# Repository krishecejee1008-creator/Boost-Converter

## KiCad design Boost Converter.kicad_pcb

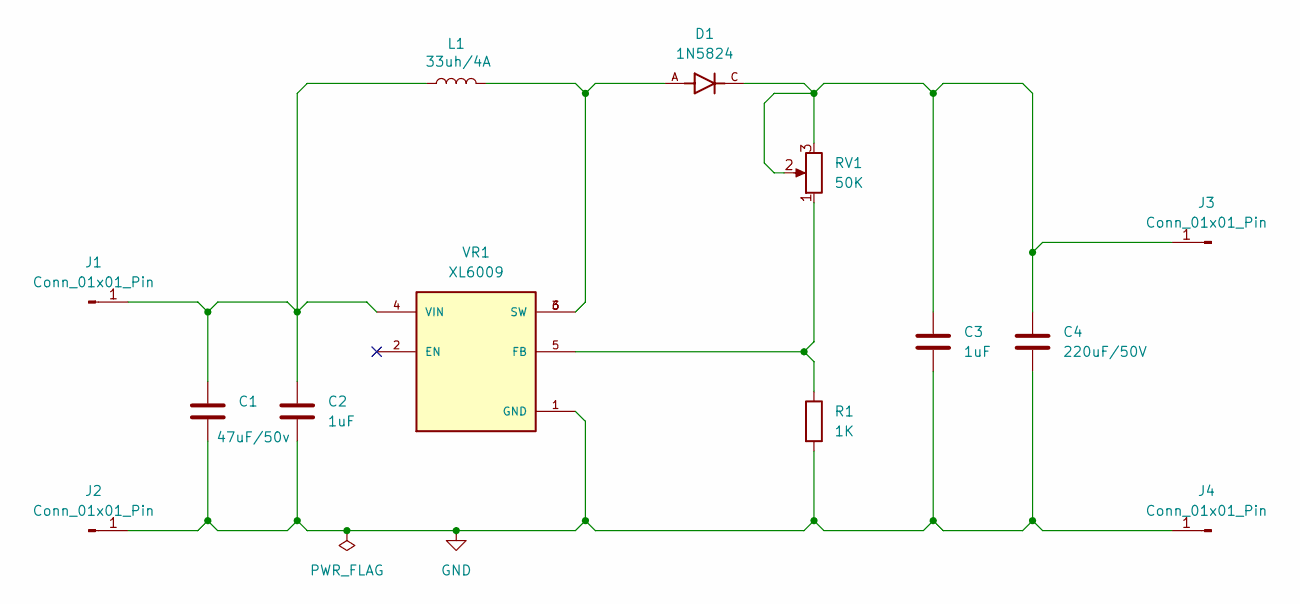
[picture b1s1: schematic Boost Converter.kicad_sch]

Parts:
C1: 47uF/50v; C_Radial_D6.3mm_H11.0mm_P2.50mm
C2, C3: 1uF; C_0805_2012Metric
C4: 220uF/50V; C_Radial_D6.3mm_H11.0mm_P2.50mm
D1: 1N5824; DIOAD1898W129L762D1143; PARTREV 2
J1, J2, J3, J4: Conn_01x01_Pin; PinHeader_1x01_P1.00mm_Vertical
L1: 33uh/4A; L_12x12mm_H8mm
R1: 1K; R_1206_3216Metric
RV1: 50K; Potentiometer_Bourns_3296W_Vertical
VR1: XL6009; DPAK170P1435X465-6N; PARTREV 1.1

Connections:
GND: C1.2, C2.2, C3.2, C4.2, J2.1, J4.1, R1.2, VR1.1 (GND)
unnamed: D1.A, L1.2, VR1.3 (SW), VR1.6 (SW)
unnamed: C1.1, C2.1, J1.1, L1.1, VR1.4 (VIN)
unnamed: C3.1, C4.1, D1.C, J3.1, RV1.2, RV1.3
unnamed: R1.1, RV1.1, VR1.5 (FB)

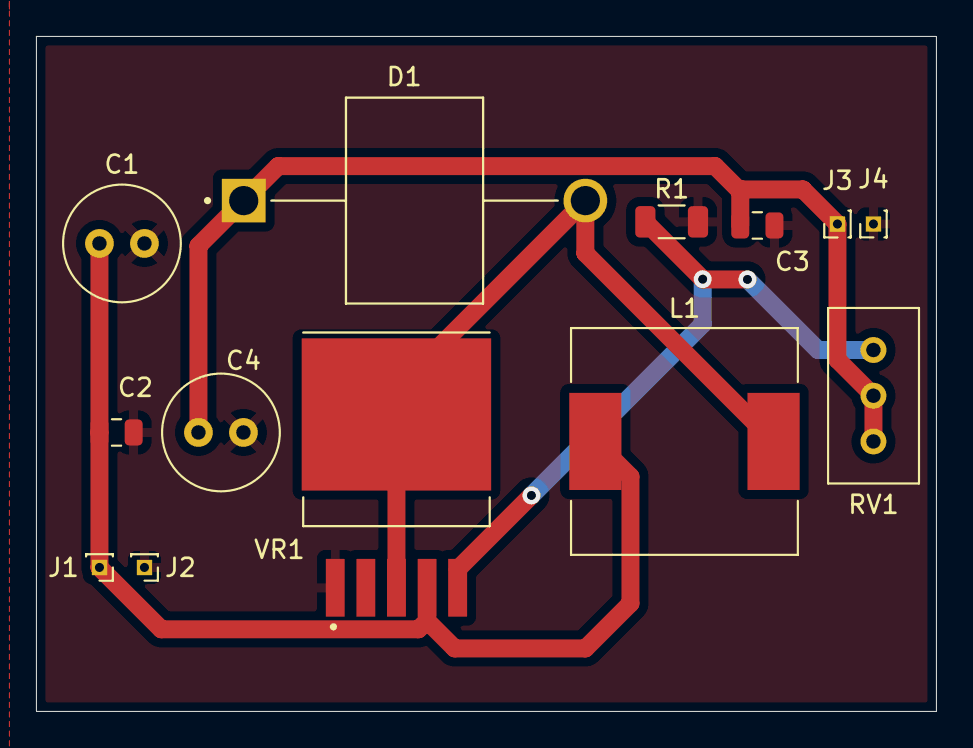
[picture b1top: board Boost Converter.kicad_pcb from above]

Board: 2 copper layers, 50.0 x 37.5 mm, 13 parts (0 on the bottom side), 5 nets.
